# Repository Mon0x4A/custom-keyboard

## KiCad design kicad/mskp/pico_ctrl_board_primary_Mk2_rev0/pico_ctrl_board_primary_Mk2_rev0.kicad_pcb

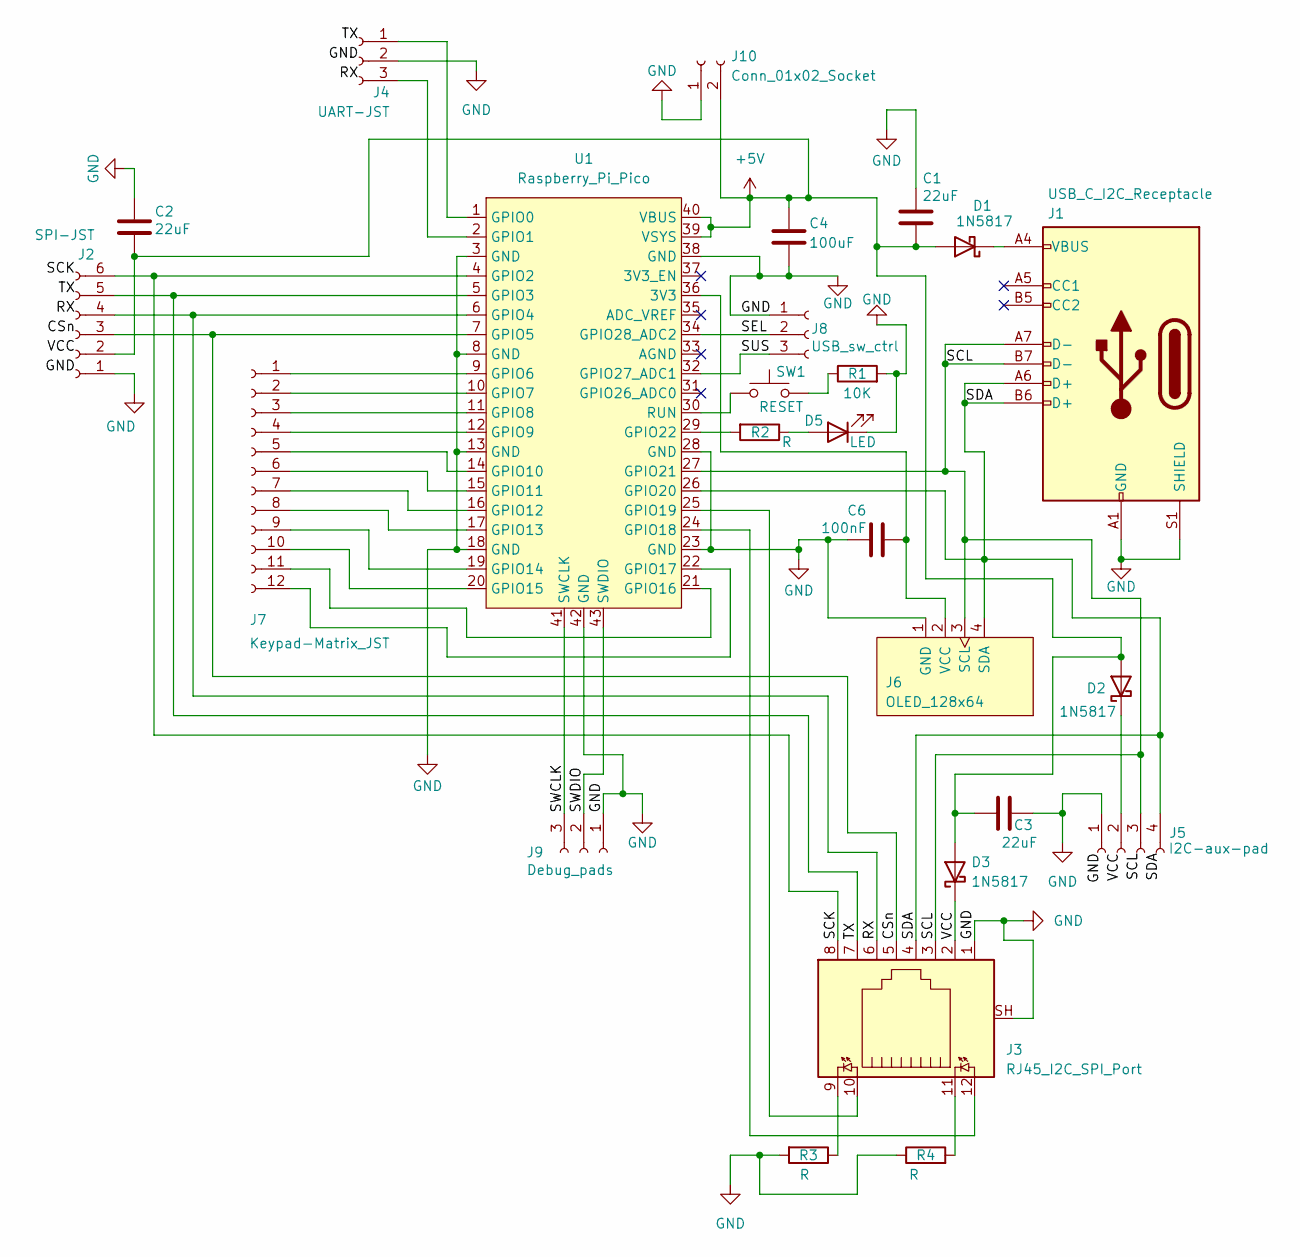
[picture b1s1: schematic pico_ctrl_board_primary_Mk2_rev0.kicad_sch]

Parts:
C1, C2, C3: 22uF; C_1206_3216Metric_Pad1.33x1.80mm_HandSolder
C4: 100uF; C_1206_3216Metric_Pad1.33x1.80mm_HandSolder
C6: 100nF; C_1206_3216Metric_Pad1.33x1.80mm_HandSolder
D1, D2, D3: 1N5817; D_DO-41_SOD81_P10.16mm_Horizontal
D5: LED; LED_0805_2012Metric_Pad1.15x1.40mm_HandSolder
J1: USB_C_I2C_Receptacle; USB_C_Receptacle_GCT_USB4110
J2: SPI-JST; JST_GH_SM06B-GHS-TB_1x06-1MP_P1.25mm_Horizontal
J3: RJ45_I2C_SPI_Port; RJ45_Amphenol_RJHSE538X
J4: UART-JST; JST_SH_SM03B-SRSS-TB_1x03-1MP_P1.00mm_Horizontal
J5: I2C-aux-pad; PinHeader_1x04_P2.54mm_Vertical
J6: OLED_128x64
J7: Keypad-Matrix_JST; JST_GH_SM12B-GHS-TB_1x12-1MP_P1.25mm_Horizontal
J8: USB_sw_ctrl; PinSocket_1x03_P2.54mm_Vertical
J9: Debug_pads; PinHeader_1x03_P2.54mm_Vertical
J10: Conn_01x02_Socket; PinHeader_1x02_P2.54mm_Vertical
R1: 10K; R_Axial_DIN0207_L6.3mm_D2.5mm_P7.62mm_Horizontal
R2, R3, R4: R; R_Axial_DIN0207_L6.3mm_D2.5mm_P7.62mm_Horizontal
SW1: RESET; SW_SPST_Omron_B3FS-101xP
U1: Raspberry_Pi_Pico

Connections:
+5V: C1.1, C2.1, C3.2, C4.1, D1.2 (A), D2.2 (A), D3.2 (A), J2.2, J10.2, U1.39 (VSYS), U1.40 (VBUS)
/CSn: J2.3, J3.5, U1.7 (GPIO5)
/RX: J2.4, J3.6, U1.6 (GPIO4)
/SCK: J2.6, J3.8, U1.4 (GPIO2)
/SCL: J1.A7 (D-), J1.B7 (D-), J3.3, J5.3, J6.3 (SCL), U1.27 (GPIO21)
/SDA: J1.A6 (D+), J1.B6 (D+), J3.4, J5.4, J6.4 (SDA), U1.26 (GPIO20)
/SEL: J8.2, U1.34 (GPIO28_ADC2)
/SUS: J8.3, U1.32 (GPIO27_ADC1)
/SWCLK: J9.3, U1.41 (SWCLK)
/SWDIO: J9.2, U1.43 (SWDIO)
/TX: J2.5, J3.7, U1.5 (GPIO3)
/VCC: D3.1 (K), J3.2
GND: C1.2, C2.2, C3.1, C4.2, C6.2, D5.1 (K), J1.A1 (GND), J1.A12 (GND), J1.B1 (GND), J1.B12 (GND), J1.S1 (SHIELD), J2.1, J3.1, J3.SH, J4.2, J5.1, J6.1 (GND), J8.1, J9.1, J10.1, R1.2, R3.2, R4.1, U1.3 (GND), U1.8 (GND), U1.13 (GND), U1.18 (GND), U1.23 (GND), U1.28 (GND), U1.38 (GND), U1.42 (GND)
unnamed: D1.1 (K), J1.A4 (VBUS), J1.A9 (VBUS), J1.B4 (VBUS), J1.B9 (VBUS)
unnamed: D2.1 (K), J5.2
unnamed: D5.2 (A), R2.1
unnamed: J3.9, R3.1
unnamed: J3.11, R4.2
unnamed: J4.1, U1.1 (GPIO0)
unnamed: J4.3, U1.2 (GPIO1)
unnamed: C6.1, J6.2 (VCC), U1.36 (3V3)
unnamed: J7.1, U1.9 (GPIO6)
unnamed: J7.2, U1.10 (GPIO7)
unnamed: J7.3, U1.11 (GPIO8)
unnamed: J7.4, U1.12 (GPIO9)
unnamed: J7.5, U1.14 (GPIO10)
unnamed: J7.6, U1.15 (GPIO11)
unnamed: J7.7, U1.16 (GPIO12)
unnamed: J7.8, U1.17 (GPIO13)
unnamed: J7.9, U1.19 (GPIO14)
unnamed: J7.10, U1.20 (GPIO15)
unnamed: J7.11, U1.21 (GPIO16)
unnamed: J7.12, U1.22 (GPIO17)
unnamed: R1.1, SW1.2
unnamed: J3.12, U1.24 (GPIO18)
unnamed: J3.10, U1.25 (GPIO19)
unnamed: R2.2, U1.29 (GPIO22)
unnamed: SW1.1, U1.30 (RUN)

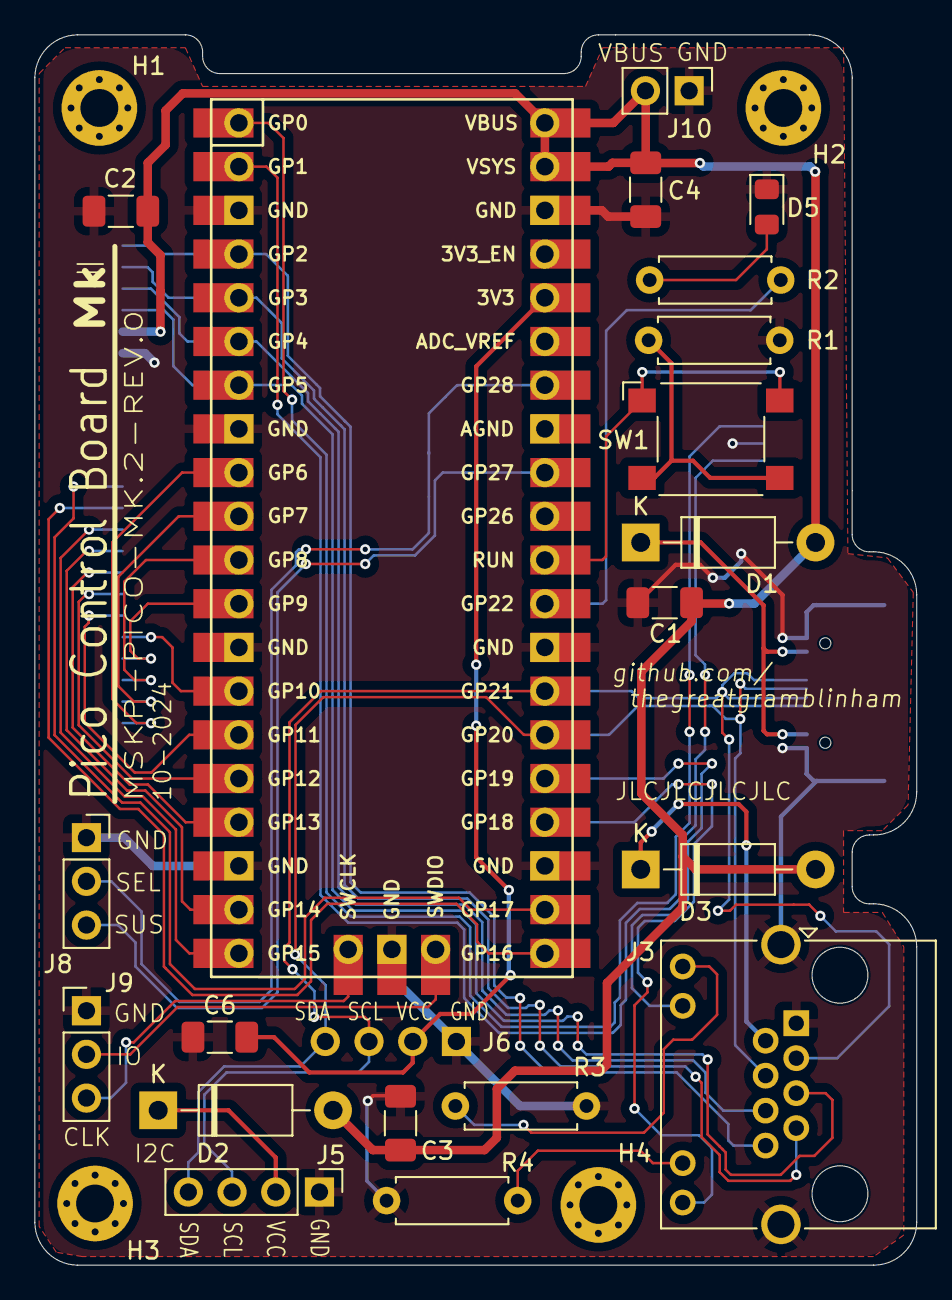
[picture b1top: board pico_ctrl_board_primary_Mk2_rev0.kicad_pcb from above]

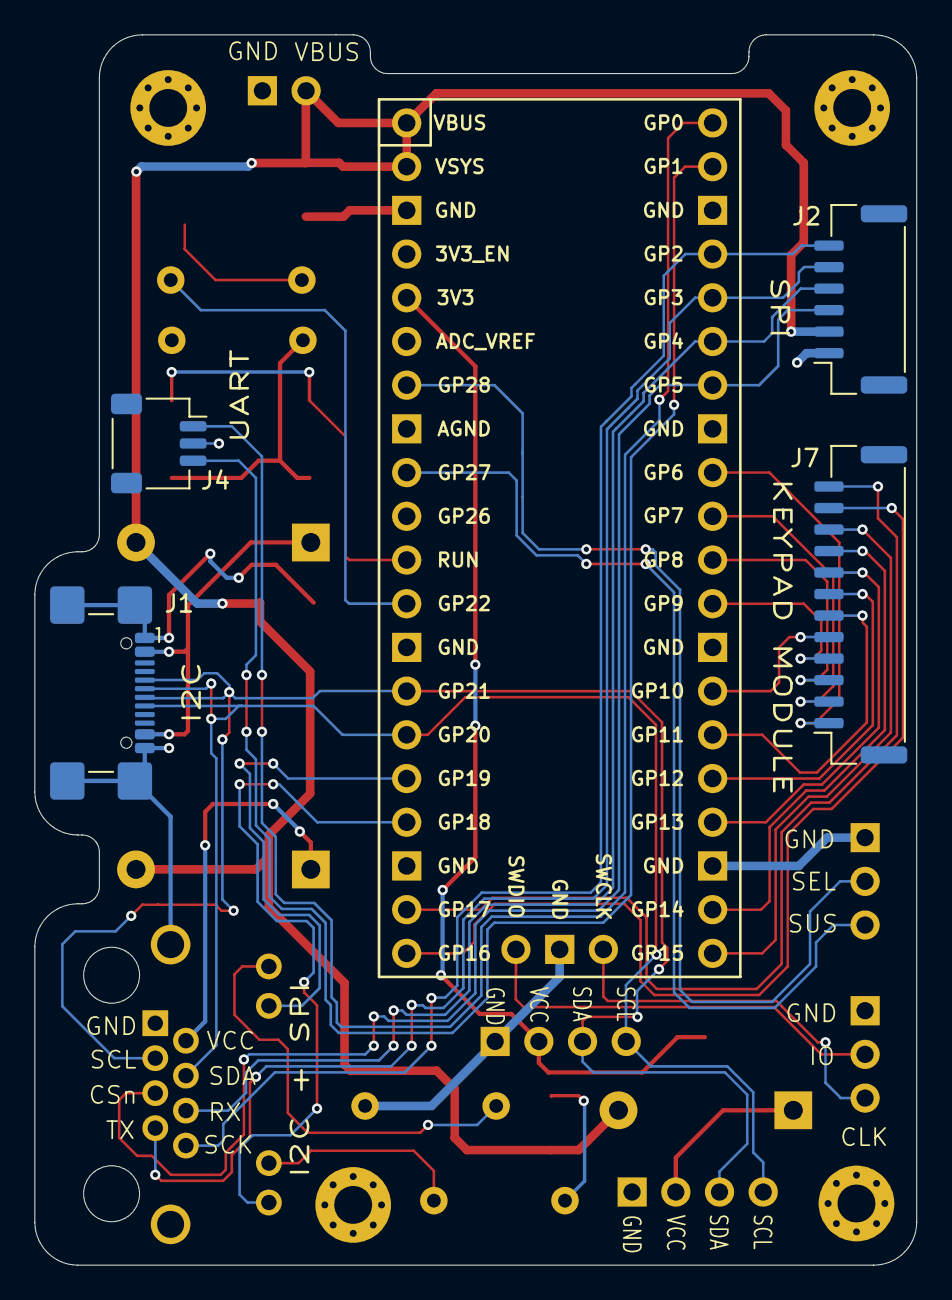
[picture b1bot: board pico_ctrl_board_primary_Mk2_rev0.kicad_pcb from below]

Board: 2 copper layers, 51.2 x 71.5 mm, 29 parts (4 on the bottom side), 38 nets.

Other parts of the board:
H1, H2, H3, H4: MountingHole_2.2mm_M2_Pad_Via

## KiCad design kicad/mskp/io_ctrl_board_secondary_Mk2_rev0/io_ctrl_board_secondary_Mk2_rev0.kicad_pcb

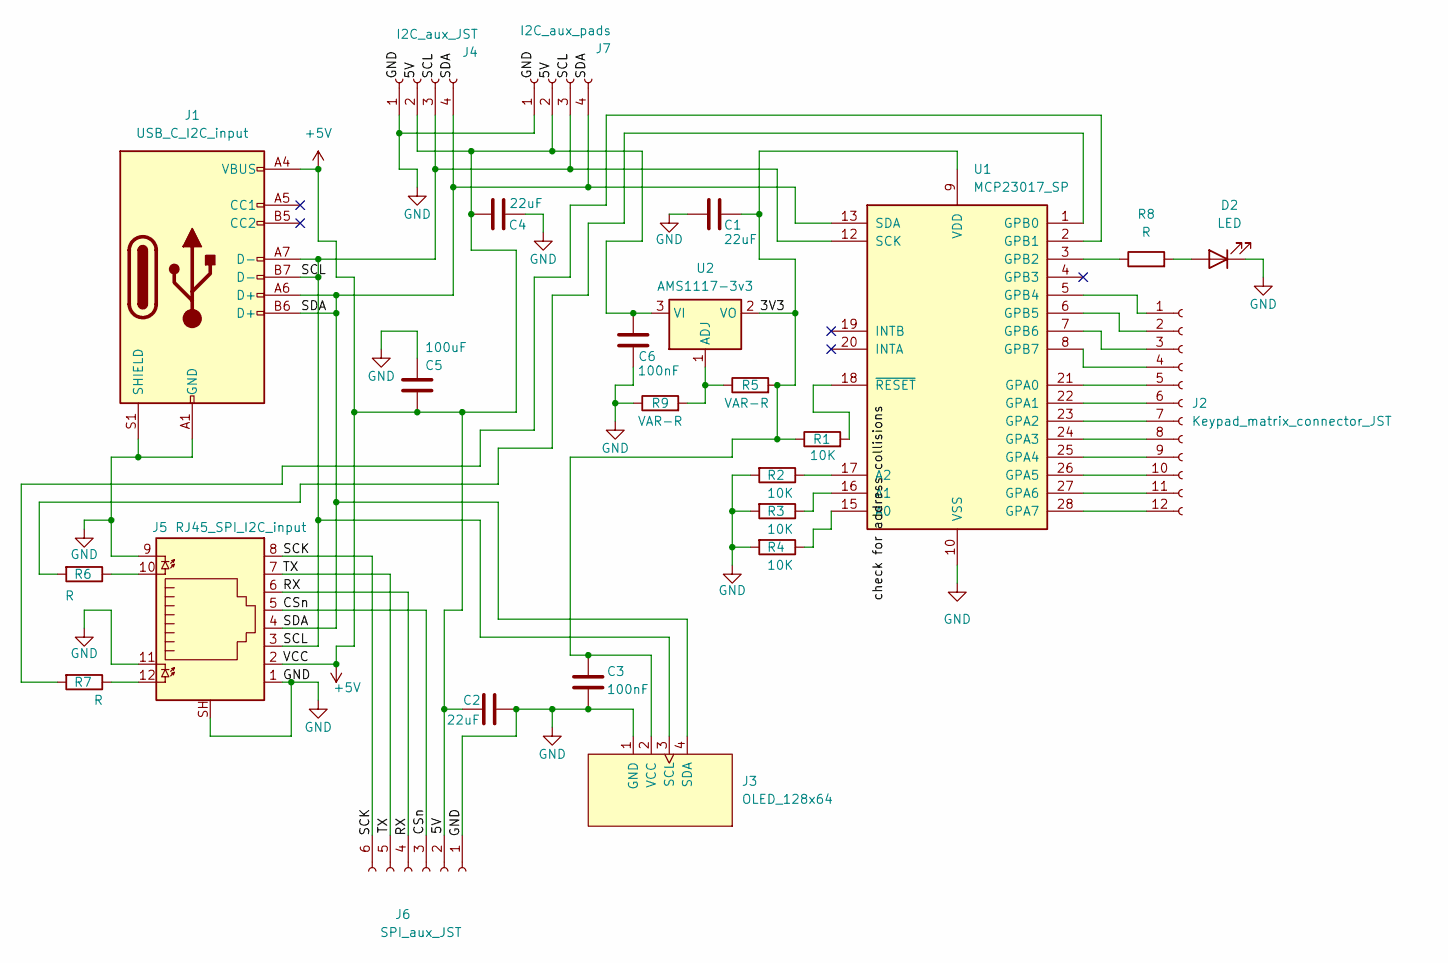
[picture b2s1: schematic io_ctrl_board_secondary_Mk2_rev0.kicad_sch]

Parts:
C1, C2, C4: 22uF; C_1206_3216Metric_Pad1.33x1.80mm_HandSolder
C3, C6: 100nF; C_1206_3216Metric_Pad1.33x1.80mm_HandSolder
C5: 100uF; C_1206_3216Metric_Pad1.33x1.80mm_HandSolder
D2: LED; LED_0805_2012Metric_Pad1.15x1.40mm_HandSolder
J1: USB_C_I2C_input; USB_C_Receptacle_GCT_USB4110
J2: Keypad_matrix_connector_JST; JST_GH_SM12B-GHS-TB_1x12-1MP_P1.25mm_Horizontal
J3: OLED_128x64
J4: I2C_aux_JST; JST_GH_SM04B-GHS-TB_1x04-1MP_P1.25mm_Horizontal
J5: RJ45_SPI_I2C_input; RJ45_Amphenol_RJHSE538X
J6: SPI_aux_JST; JST_GH_SM06B-GHS-TB_1x06-1MP_P1.25mm_Horizontal
J7: I2C_aux_pads; PinSocket_1x04_P2.54mm_Vertical
R1, R2, R3, R4: 10K; R_Axial_DIN0207_L6.3mm_D2.5mm_P7.62mm_Horizontal
R5, R9: VAR-R; R_Axial_DIN0207_L6.3mm_D2.5mm_P7.62mm_Horizontal
R6, R7, R8: R; R_Axial_DIN0207_L6.3mm_D2.5mm_P7.62mm_Horizontal
U1: MCP23017_SP; DIP-28_W7.62mm_Socket
U2: AMS1117-3v3; SOT-223-3_TabPin2

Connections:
+5V: C2.2, C4.1, C5.1, C6.2, J1.A4 (VBUS), J1.A9 (VBUS), J1.B4 (VBUS), J1.B9 (VBUS), J4.2, J5.2, J6.2, J7.2, U2.3 (VI)
/3V3: C1.1, C3.1, J3.2 (VCC), R1.1, R5.2, U1.9 (VDD), U2.2 (VO)
/CSn: J5.5, J6.3
/RX: J5.6, J6.4
/SCK: J5.8, J6.6
/SCL: J1.A7 (D-), J1.B7 (D-), J3.3 (SCL), J4.3, J5.3, J7.3, U1.12 (SCK)
/SDA: J1.A6 (D+), J1.B6 (D+), J3.4 (SDA), J4.4, J5.4, J7.4, U1.13 (SDA)
/TX: J5.7, J6.5
GND: C1.2, C2.1, C3.2, C4.2, C5.2, C6.1, D2.1 (K), J1.A1 (GND), J1.A12 (GND), J1.B1 (GND), J1.B12 (GND), J1.S1 (SHIELD), J3.1 (GND), J4.1, J5.1, J5.9, J5.11, J5.SH, J6.1, J7.1, R2.2, R3.2, R4.2, R9.1, U1.10 (VSS)
unnamed: D2.2 (A), R8.2
unnamed: J2.1, U1.5 (GPB4)
unnamed: J2.2, U1.6 (GPB5)
unnamed: J2.3, U1.7 (GPB6)
unnamed: J2.4, U1.8 (GPB7)
unnamed: J2.5, U1.21 (GPA0)
unnamed: J2.6, U1.22 (GPA1)
unnamed: J2.7, U1.23 (GPA2)
unnamed: J2.8, U1.24 (GPA3)
unnamed: J2.9, U1.25 (GPA4)
unnamed: J2.10, U1.26 (GPA5)
unnamed: J2.11, U1.27 (GPA6)
unnamed: J2.12, U1.28 (GPA7)
unnamed: J5.10, R6.1
unnamed: J5.12, R7.1
unnamed: R4.1, U1.15 (A0)
unnamed: R3.1, U1.16 (A1)
unnamed: R2.1, U1.17 (A2)
unnamed: R6.2, U1.1 (GPB0)
unnamed: R7.2, U1.2 (GPB1)
unnamed: R8.1, U1.3 (GPB2)
unnamed: R1.2, U1.18 (~RESET)
unnamed: R5.1, R9.2, U2.1 (ADJ)

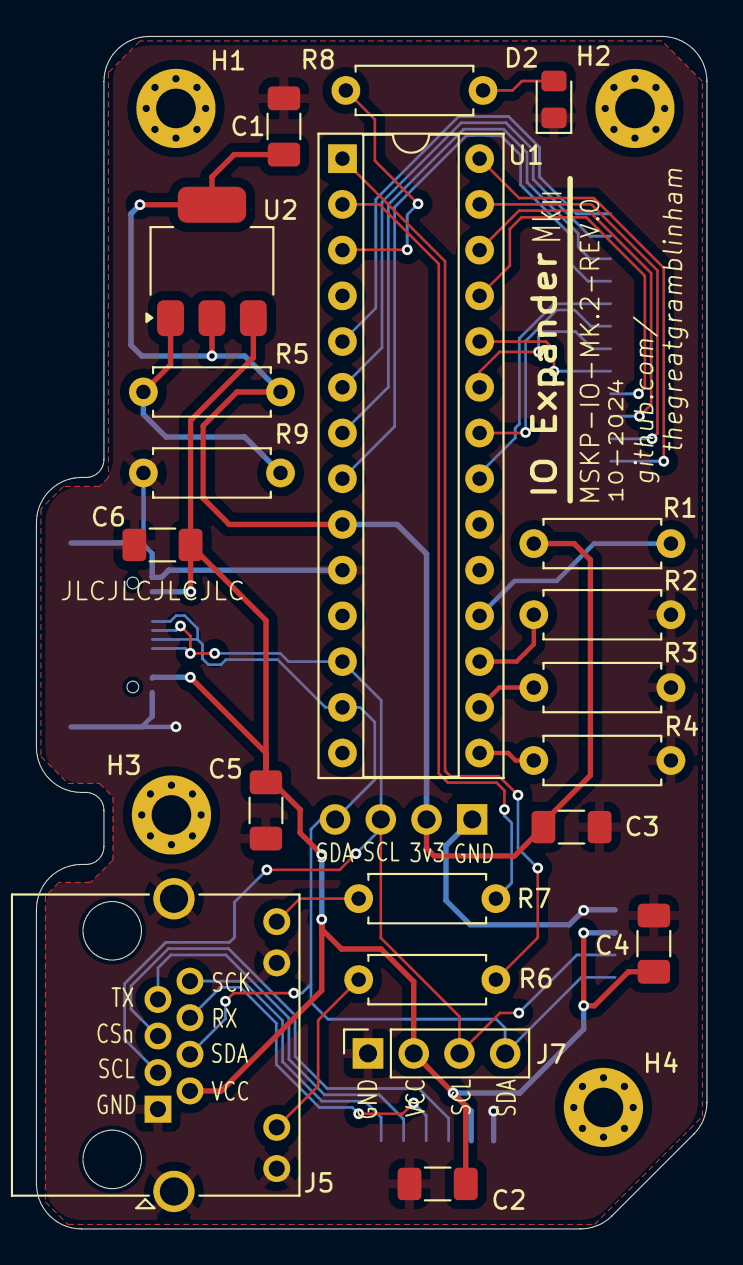
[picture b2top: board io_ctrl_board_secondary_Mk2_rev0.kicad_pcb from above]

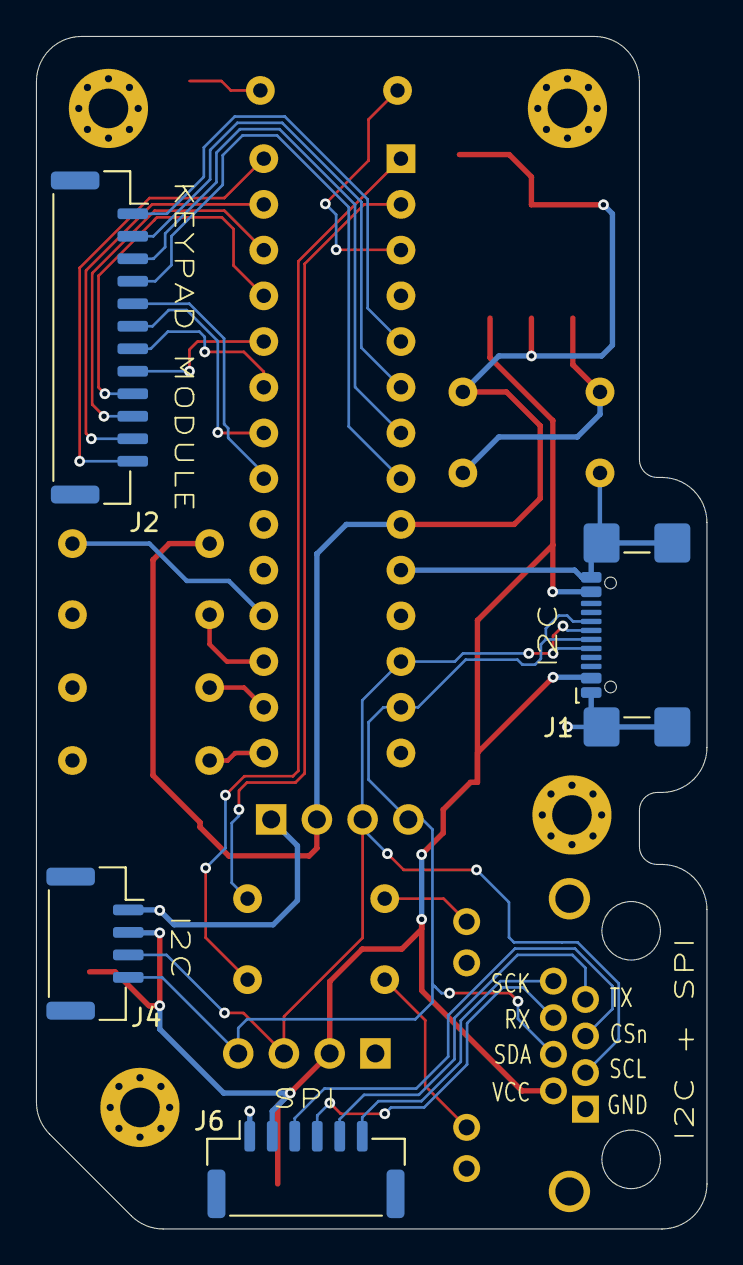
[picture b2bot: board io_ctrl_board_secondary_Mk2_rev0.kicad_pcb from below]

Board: 2 copper layers, 37.2 x 66.2 mm, 29 parts (4 on the bottom side), 32 nets.

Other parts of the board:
H1, H2, H3, H4: MountingHole_2.2mm_M2_Pad_Via

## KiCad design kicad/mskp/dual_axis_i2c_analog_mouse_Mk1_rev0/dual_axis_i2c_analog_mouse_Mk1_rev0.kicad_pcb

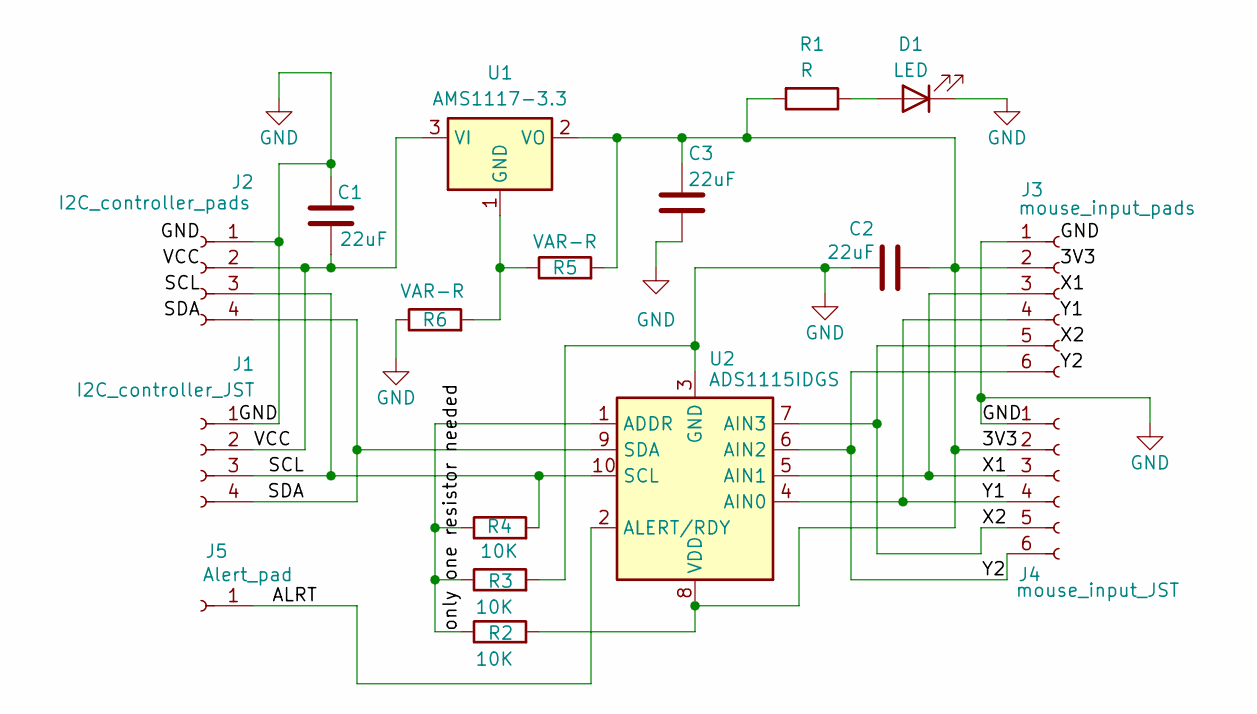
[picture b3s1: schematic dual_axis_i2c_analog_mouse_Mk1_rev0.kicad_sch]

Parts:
C1, C2, C3: 22uF; C_1206_3216Metric_Pad1.33x1.80mm_HandSolder
D1: LED; LED_0805_2012Metric_Pad1.15x1.40mm_HandSolder
J1: I2C_controller_JST; JST_GH_SM04B-GHS-TB_1x04-1MP_P1.25mm_Horizontal
J2: I2C_controller_pads; PinSocket_1x04_P2.54mm_Vertical
J3: mouse_input_pads; PinSocket_1x06_P2.54mm_Vertical
J4: mouse_input_JST; JST_GH_SM06B-GHS-TB_1x06-1MP_P1.25mm_Horizontal
J5: Alert_pad; PinSocket_1x01_P2.54mm_Vertical
R1: R; R_Axial_DIN0207_L6.3mm_D2.5mm_P7.62mm_Horizontal
R2, R3, R4: 10K; R_Axial_DIN0207_L6.3mm_D2.5mm_P7.62mm_Horizontal
R5, R6: VAR-R; R_Axial_DIN0207_L6.3mm_D2.5mm_P7.62mm_Horizontal
U1: AMS1117-3.3; SOT-223-3_TabPin2
U2: ADS1115IDGS; TSSOP-10_3x3mm_P0.5mm

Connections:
/3V3: C2.2, C3.1, J3.2, J4.2, R1.2, R2.2, R5.2, U1.2 (VO), U2.8 (VDD)
/ALRT: J5.1, U2.2 (ALERT/RDY)
/SCL: J1.3, J2.3, R4.2, U2.10 (SCL)
/SDA: J1.4, J2.4, U2.9 (SDA)
/VCC: C1.2, J1.2, J2.2, U1.3 (VI)
/X1: J3.3, J4.3, U2.5 (AIN1)
/X2: J3.5, J4.5, U2.7 (AIN3)
/Y1: J3.4, J4.4, U2.4 (AIN0)
/Y2: J3.6, J4.6, U2.6 (AIN2)
/only one resistor needed: R2.1, R3.1, R4.1, U2.1 (ADDR)
GND: C1.1, C2.1, C3.2, D1.1 (K), J1.1, J2.1, J3.1, J4.1, R3.2, R6.1, U2.3 (GND)
unnamed: D1.2 (A), R1.1
unnamed: R5.1, R6.2, U1.1 (GND)

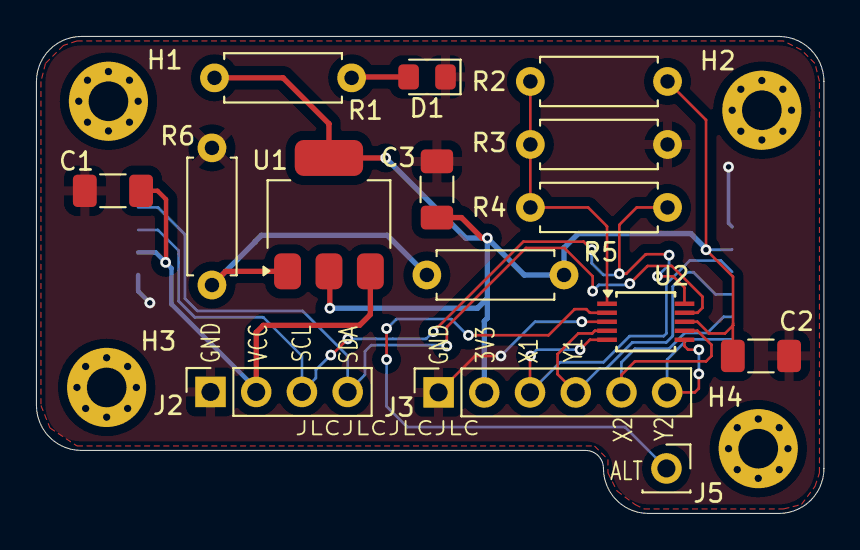
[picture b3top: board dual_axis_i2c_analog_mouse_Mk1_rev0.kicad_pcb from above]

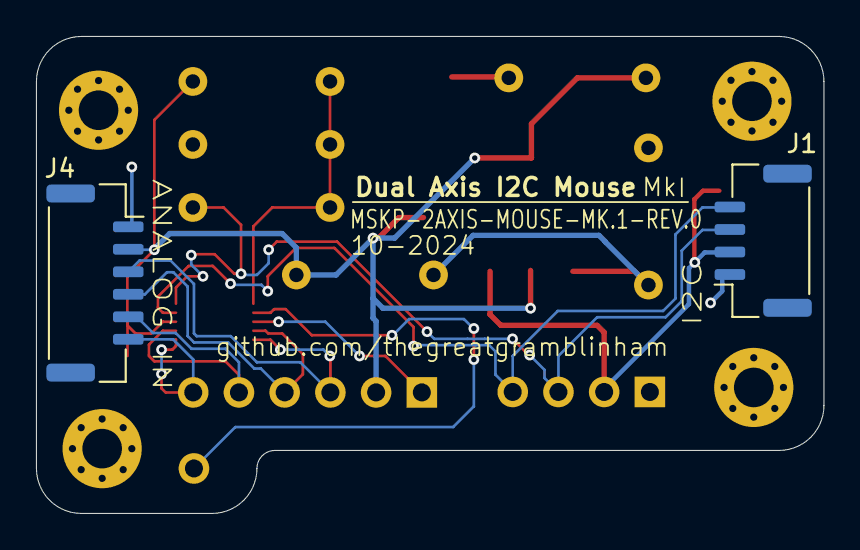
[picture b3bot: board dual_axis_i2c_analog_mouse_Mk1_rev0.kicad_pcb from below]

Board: 2 copper layers, 43.8 x 26.5 mm, 21 parts (2 on the bottom side), 13 nets.

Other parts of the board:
H1, H2, H3, H4: MountingHole_2.2mm_M2_Pad_Via

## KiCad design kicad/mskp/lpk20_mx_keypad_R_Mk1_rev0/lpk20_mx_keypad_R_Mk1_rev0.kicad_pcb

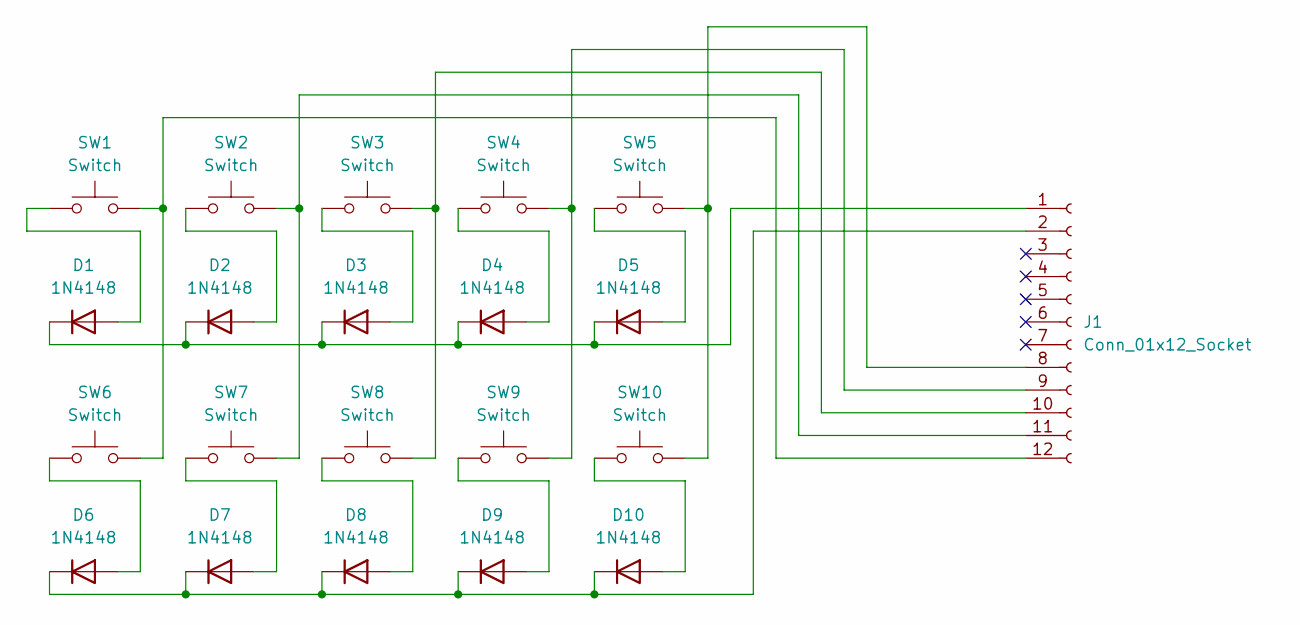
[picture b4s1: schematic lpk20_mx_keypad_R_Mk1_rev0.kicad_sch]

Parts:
D1, D2, D3, D4, D5, D6, D7, D8, D9, D10: 1N4148; D_DO-35_SOD27_P7.62mm_Horizontal
J1: Conn_01x12_Socket; JST_GH_BM12B-GHS-TBT_1x12-1MP_P1.25mm_Vertical
SW1, SW2, SW3, SW4, SW5, SW6, SW7, SW8, SW9, SW10: Switch; Hotswap_MX_Plated_1.00u

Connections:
unnamed: D1.2 (A), SW1.1
unnamed: D1.1 (K), D2.1 (K), D3.1 (K), D4.1 (K), D5.1 (K), J1.1
unnamed: D2.2 (A), SW2.1
unnamed: D3.2 (A), SW3.1
unnamed: D4.2 (A), SW4.1
unnamed: D5.2 (A), SW5.1
unnamed: D6.2 (A), SW6.1
unnamed: D7.2 (A), SW7.1
unnamed: D8.2 (A), SW8.1
unnamed: D9.2 (A), SW9.1
unnamed: D10.2 (A), SW10.1
unnamed: D6.1 (K), D7.1 (K), D8.1 (K), D9.1 (K), D10.1 (K), J1.2
unnamed: J1.8, SW5.2, SW10.2
unnamed: J1.9, SW4.2, SW9.2
unnamed: J1.10, SW3.2, SW8.2
unnamed: J1.11, SW2.2, SW7.2
unnamed: J1.12, SW1.2, SW6.2

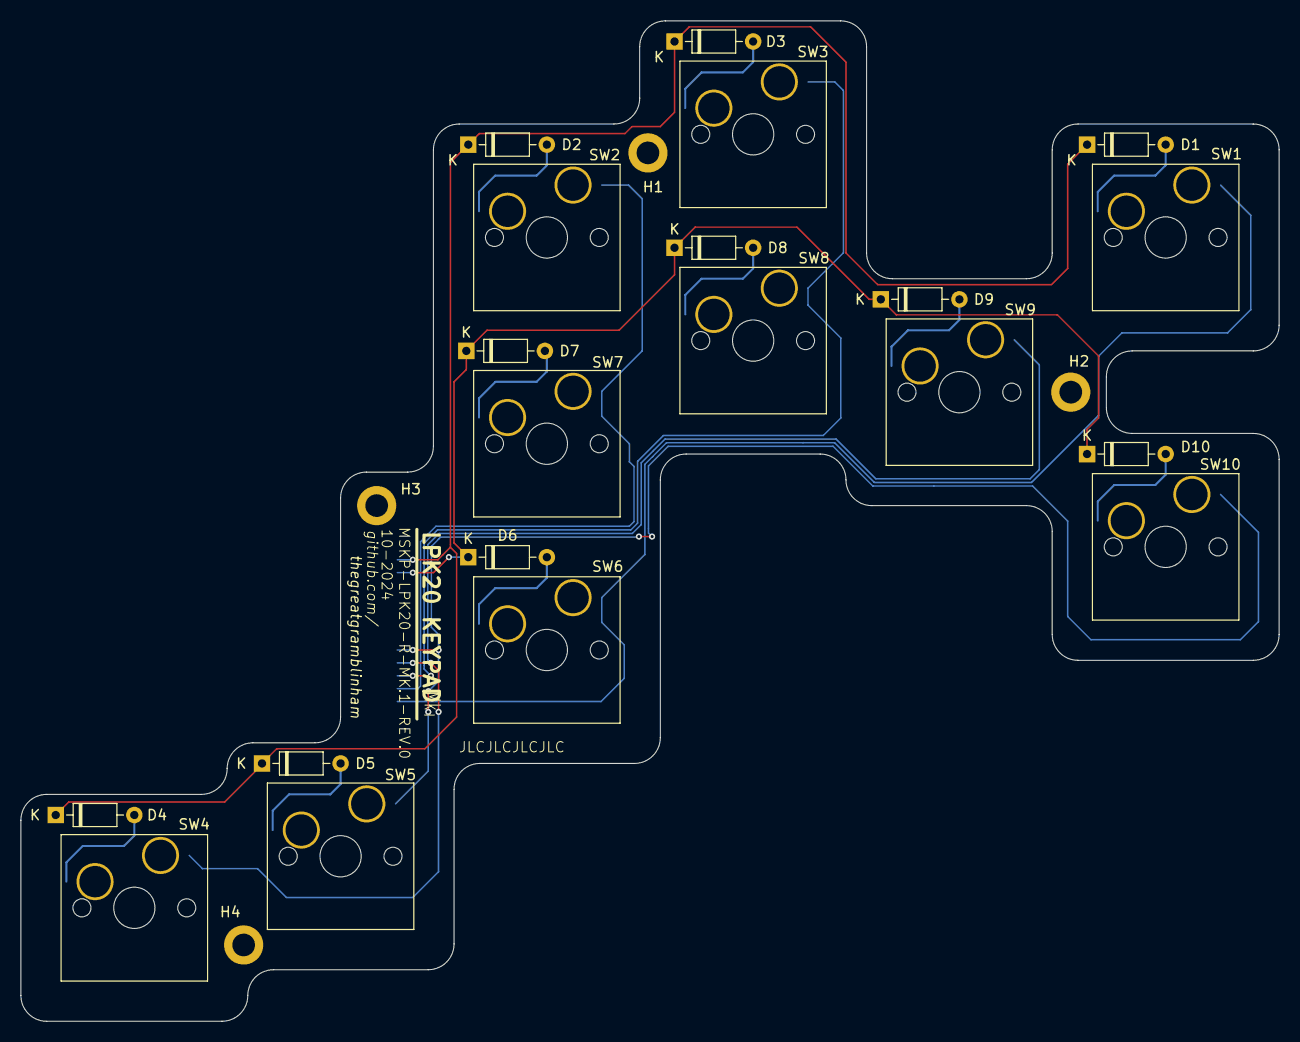
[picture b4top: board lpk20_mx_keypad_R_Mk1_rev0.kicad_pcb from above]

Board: 2 copper layers, 122.0 x 97.0 mm, 25 parts (1 on the bottom side), 17 nets.

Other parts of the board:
H1, H2, H3, H4: MountingHole_2.2mm_M2_ISO14580_Pad

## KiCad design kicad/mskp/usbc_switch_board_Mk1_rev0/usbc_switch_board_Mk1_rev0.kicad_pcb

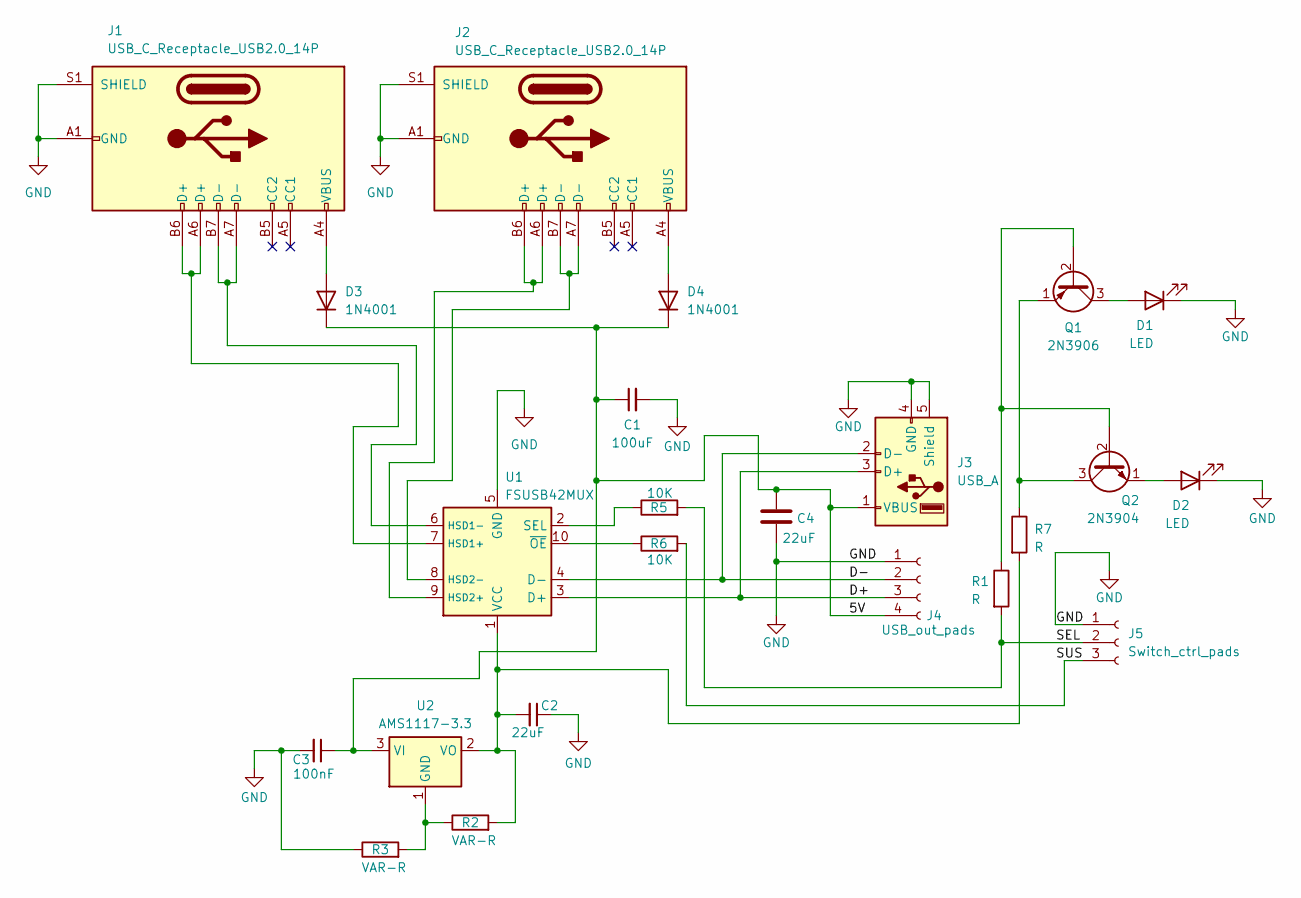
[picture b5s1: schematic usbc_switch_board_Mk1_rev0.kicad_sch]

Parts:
C1: 100uF; C_1206_3216Metric_Pad1.33x1.80mm_HandSolder
C2, C4: 22uF; C_1206_3216Metric_Pad1.33x1.80mm_HandSolder
C3: 100nF; C_1206_3216Metric_Pad1.33x1.80mm_HandSolder
D1, D2: LED; LED_0805_2012Metric_Pad1.15x1.40mm_HandSolder
D3, D4: 1N4001; D_DO-41_SOD81_P10.16mm_Horizontal
J1, J2: USB_C_Receptacle_USB2.0_14P; USB_C_Receptacle_GCT_USB4110
J3: USB_A; USB_A_CONNFLY_DS1095-WNR0
J4: USB_out_pads; PinHeader_1x04_P2.54mm_Vertical
J5: Switch_ctrl_pads; PinSocket_1x03_P2.54mm_Vertical
Q1: 2N3906; TO-92_Inline
Q2: 2N3904; TO-92_Inline
R1, R7: R; R_Axial_DIN0207_L6.3mm_D2.5mm_P7.62mm_Horizontal
R2, R3: VAR-R; R_Axial_DIN0207_L6.3mm_D2.5mm_P7.62mm_Horizontal
R5, R6: 10K; R_Axial_DIN0207_L6.3mm_D2.5mm_P7.62mm_Horizontal
U1: FSUSB42MUX; MSOP-10_3x3mm_P0.5mm
U2: AMS1117-3.3; SOT-223-3_TabPin2

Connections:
/5V: C1.1, C3.1, C4.1, D3.1 (K), D4.1 (K), J3.1 (VBUS), J4.4, U2.3 (VI)
/D+: J3.3 (D+), J4.3, U1.3 (D+)
/D-: J3.2 (D-), J4.2, U1.4 (D-)
/SEL: J5.2, R1.2, R5.2
GND: C1.2, C2.1, C3.2, C4.2, D1.1 (K), D2.1 (K), J1.A1 (GND), J1.A12 (GND), J1.B1 (GND), J1.B12 (GND), J1.S1 (SHIELD), J2.A1 (GND), J2.A12 (GND), J2.B1 (GND), J2.B12 (GND), J2.S1 (SHIELD), J3.4 (GND), J3.5 (Shield), J4.1, J5.1, R3.1, U1.5 (GND)
unnamed: D1.2 (A), Q1.3 (C)
unnamed: D2.2 (A), Q2.1 (E)
unnamed: D3.2 (A), J1.A4 (VBUS), J1.A9 (VBUS), J1.B4 (VBUS), J1.B9 (VBUS)
unnamed: D4.2 (A), J2.A4 (VBUS), J2.A9 (VBUS), J2.B4 (VBUS), J2.B9 (VBUS)
unnamed: J5.3, R6.2
unnamed: Q1.2 (B), Q2.2 (B), R1.1
unnamed: Q1.1 (E), Q2.3 (C), R7.1
unnamed: J1.A6 (D+), J1.B6 (D+), U1.7 (HSD1+)
unnamed: J1.A7 (D-), J1.B7 (D-), U1.6 (HSD1-)
unnamed: J2.A6 (D+), J2.B6 (D+), U1.9 (HSD2+)
unnamed: J2.A7 (D-), J2.B7 (D-), U1.8 (HSD2-)
unnamed: R5.1, U1.2 (SEL)
unnamed: C2.2, R2.2, R7.2, U1.1 (VCC), U2.2 (VO)
unnamed: R6.1, U1.10 (~OE)
unnamed: R2.1, R3.2, U2.1 (GND)

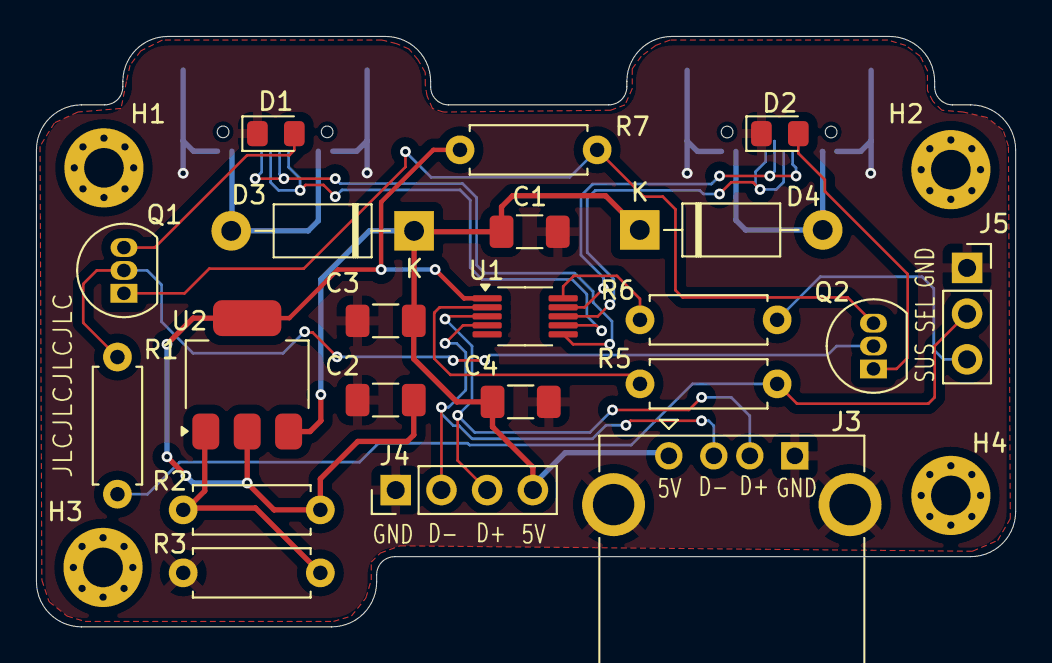
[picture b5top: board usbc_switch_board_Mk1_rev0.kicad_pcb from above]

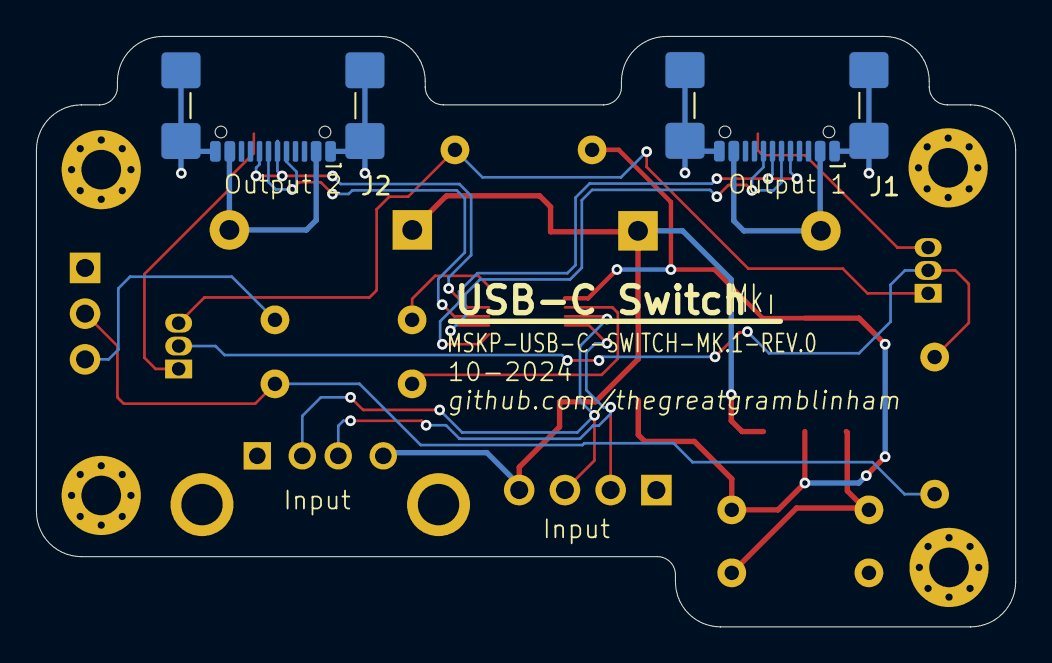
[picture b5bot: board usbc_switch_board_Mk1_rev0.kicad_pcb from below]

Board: 2 copper layers, 54.4 x 32.8 mm, 27 parts (2 on the bottom side), 20 nets.

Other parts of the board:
H1, H2, H3, H4: MountingHole_2.2mm_M2_Pad_Via
